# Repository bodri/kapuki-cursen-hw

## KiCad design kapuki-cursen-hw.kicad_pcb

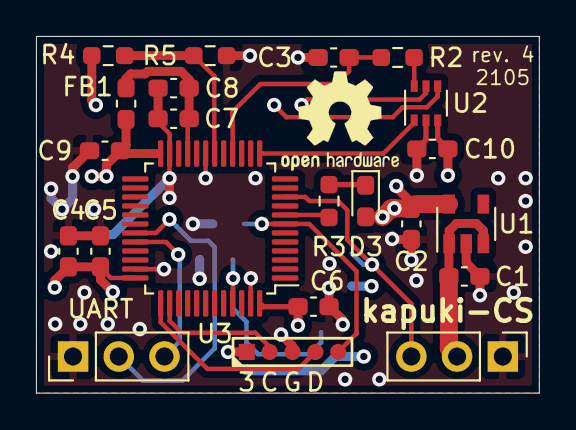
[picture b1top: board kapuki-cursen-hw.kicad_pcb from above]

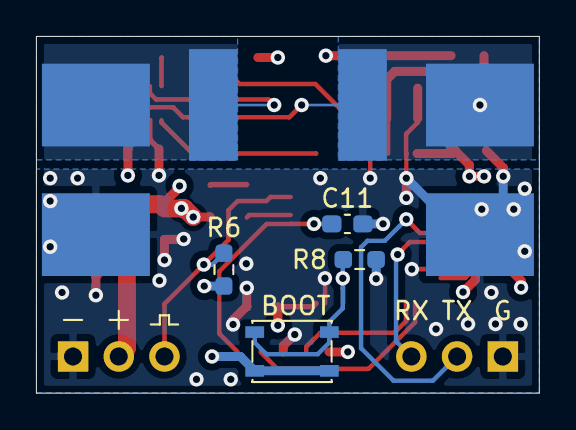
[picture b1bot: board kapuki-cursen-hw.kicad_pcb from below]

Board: 4 copper layers, 27.9 x 19.8 mm, 29 parts (7 on the bottom side), 21 nets.

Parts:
C1: 1.0uF; C_0603_1608Metric_Pad1.08x0.95mm_HandSolder
C2: 2.2uF; C_0603_1608Metric_Pad1.08x0.95mm_HandSolder
C3: 100pF; C_0603_1608Metric_Pad1.08x0.95mm_HandSolder
C4: 4.7uF; C_0603_1608Metric_Pad1.08x0.95mm_HandSolder
C5, C6, C9, C11: 100nF; C_0603_1608Metric_Pad1.08x0.95mm_HandSolder
C7: 1uF; C_0603_1608Metric_Pad1.08x0.95mm_HandSolder
C8: 10nF; C_0603_1608Metric_Pad1.08x0.95mm_HandSolder
C10: 100n; C_0603_1608Metric_Pad1.08x0.95mm_HandSolder
D3: LED; LED_0603_1608Metric_Pad1.05x0.95mm_HandSolder
FB1: 100 @ 100MHz; L_0603_1608Metric_Pad1.05x0.95mm_HandSolder
J1, J2: Conn_01x02; XT60
J3, J7: Conn_01x03; PinHeader_1x03_P2.54mm_Vertical
J8: Conn_01x05; TestPoint_5Pad_D0.8mm
R1: 0.0002ohm 1% 12W; Bourns_ CSS2H
R2, R3: 1k; R_0603_1608Metric_Pad0.98x0.95mm_HandSolder
R4: 18k 1%; R_0603_1608Metric_Pad0.98x0.95mm_HandSolder
R5: 2k4 1%; R_0603_1608Metric_Pad0.98x0.95mm_HandSolder
R6: 4k7; R_0603_1608Metric_Pad0.98x0.95mm_HandSolder
R8: 10k; R_0603_1608Metric_Pad0.98x0.95mm_HandSolder
SW1: BOOT; SW_SPST_PTS810
U1: MIC5235; SOT-23-5
U2: INA199; SOT-363_SC-70-6
U3: STM32G431CBTx; LQFP-48_7x7mm_P0.5mm

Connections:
+3V3: C2.1, C4.1, C5.1, C6.1, C9.1, C10.2, D3.2, FB1.2, J8.1, R6.2, SW1.1, U1.5, U2.3, U3.24, U3.36, U3.48
/IMEAS: C3.1, R2.1, U3.16
/REF: U2.1, U3.13
/RX: J7.3, U3.32
/RXTX: J3.3, R6.1, U3.10
/SWCLK: J8.2, U3.38
/SWDIO: J8.4, U3.37
/TX: J7.2, U3.31
/UMEAS: R4.1, R5.2, U3.18
/~RESET~: C11.1, J8.5, U3.7
GND: C1.2, C2.2, C3.2, C4.2, C5.2, C6.2, C7.2, C8.2, C9.2, C10.1, C11.2, J1.1, J2.1, J3.1, J7.1, J8.3, R5.1, R8.1, U1.2, U2.2, U3.19, U3.23, U3.35, U3.47
unnamed: D3.1, R3.2
unnamed: J1.2, R1.1, R4.2
unnamed: J2.2, R1.4
unnamed: R1.2, U2.4
unnamed: R1.3, U2.5
unnamed: R2.2, U2.6
unnamed: R3.1, U3.8
unnamed: R8.2, SW1.2, U3.45
VCC: C1.1, J3.2, U1.1, U1.3
VDDA: C7.1, C8.1, FB1.1, U3.21

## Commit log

2019-11-17 Routing rev.1
2019-11-19 Send to OSHPark
2020-01-30 Rev. 2
2020-02-10 Add precision voltage reference
2020-03-01 Fix SWD connector and servo connector
2021-02-02 Replace some components
2021-02-02 Remove motor RPM measurement capability
2021-02-02 Add features for the new CPU
2021-02-04 Start the rev. 4 PCb design
2021-02-04 rev. 4 routing is almost finished
2021-02-05 Finished rev. 4
2021-02-05 Be more specific on componenet values
2021-02-05 Add 3D front image
